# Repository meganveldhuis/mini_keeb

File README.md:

# Mini Keeb

## Hardware

### Components

- 16 Cherry MX Switches
- 2 rotary encoders
- 1 128x64 OLED (0.96")

### Schematic

### PCB

( slightly outdated screenshots )

## Software

coming soon

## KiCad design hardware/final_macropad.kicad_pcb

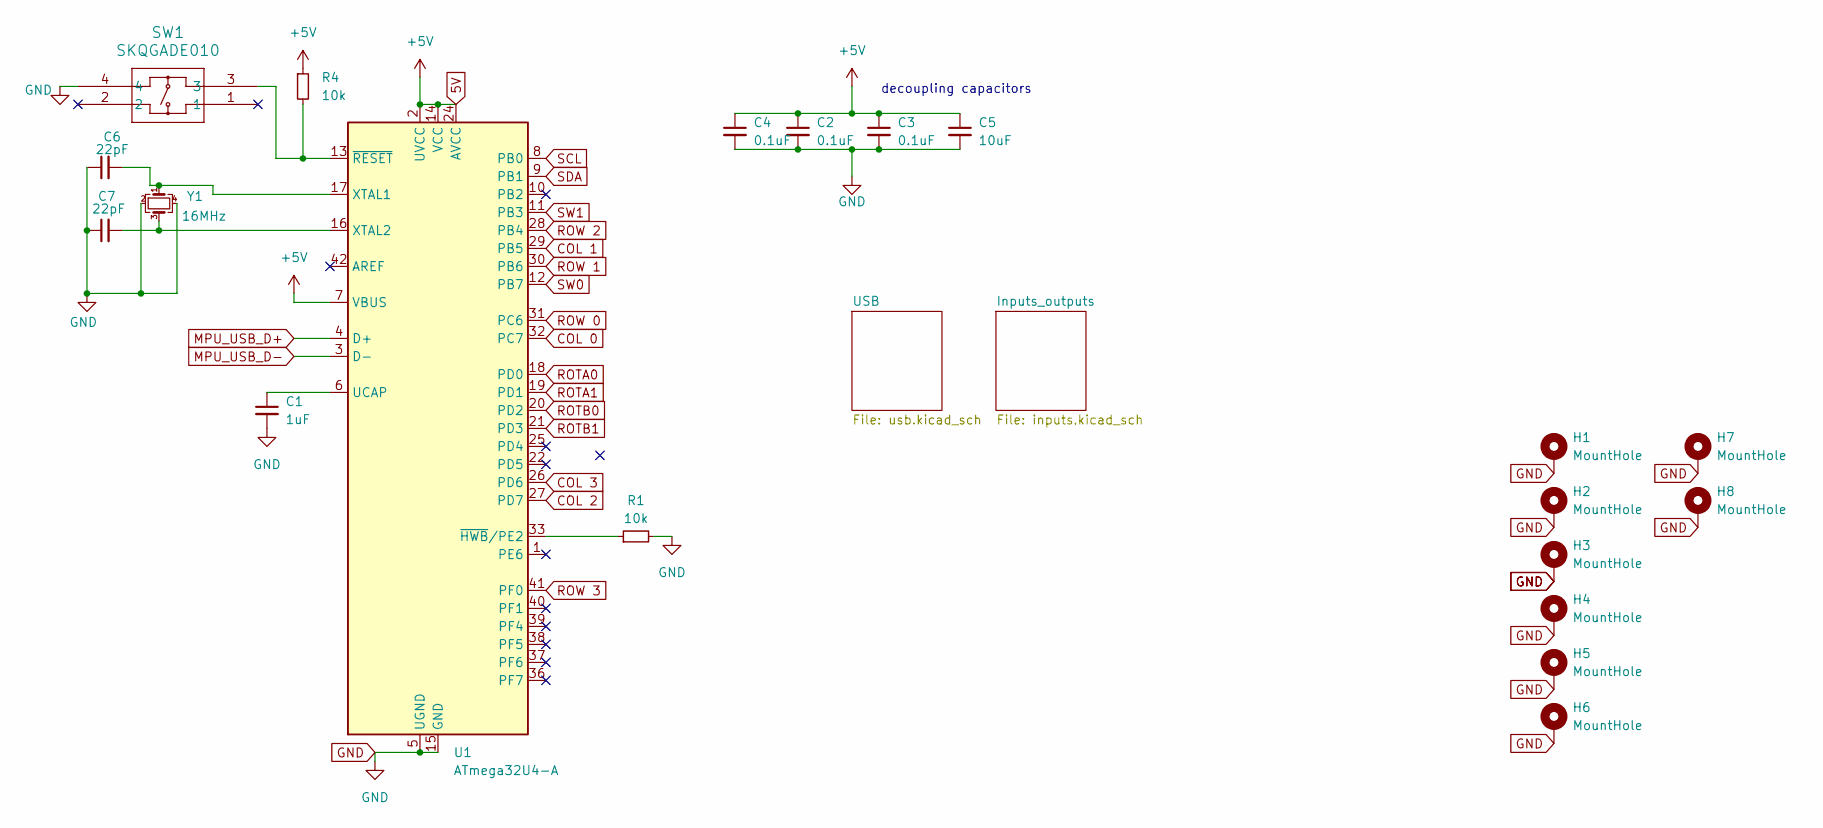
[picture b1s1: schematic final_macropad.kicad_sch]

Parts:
C1: 1uF; C_0402_1005Metric_Pad0.74x0.62mm_HandSolder
C2, C3, C4: 0.1uF; C_0402_1005Metric_Pad0.74x0.62mm_HandSolder
C5: 10uF; C_0603_1608Metric_Pad1.08x0.95mm_HandSolder
C6, C7: 22pF; C_0805_2012Metric
H1, H2, H3, H4: MountHole; MountingHole_3.2mm_M3_Pad_Via
H5, H6, H7, H8: MountHole; MountingHole_2.2mm_M2_Pad
R1, R4: 10k; R_0805_2012Metric
SW1: SKQGADE010; SKQGADE010_AAL
U1: ATmega32U4-A; TQFP-44_10x10mm_P0.8mm
Y1: 16MHz; Crystal_SMD_3225-4Pin_3.2x2.5mm

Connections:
5V: C2.1, C3.1, C4.1, C5.1, R4.1, U1.2 (UVCC), U1.7 (VBUS), U1.14 (VCC), U1.24 (AVCC), U1.34 (VCC), U1.44 (AVCC); also elsewhere on the board
COL 0: U1.32 (PC7); also elsewhere on the board
COL 1: U1.29 (PB5); also elsewhere on the board
COL 2: U1.27 (PD7); also elsewhere on the board
COL 3: U1.26 (PD6); also elsewhere on the board
GND: C1.2, C2.2, C3.2, C4.2, C5.2, C6.1, C7.1, H1.1, H2.1, H3.1, H4.1, H5.1, H6.1, H7.1, H8.1, R1.2, SW1.4, U1.5 (UGND), U1.15 (GND), U1.23 (GND), U1.35 (GND), U1.43 (GND), Y1.2, Y1.4; also elsewhere on the board
MPU_USB_D+: U1.4 (D+); also elsewhere on the board
MPU_USB_D-: U1.3 (D-); also elsewhere on the board
unnamed: C1.1, U1.6 (UCAP)
unnamed: C6.2, U1.17 (XTAL1), Y1.1
unnamed: C7.2, U1.16 (XTAL2), Y1.3
unnamed: R1.1, U1.33 (~HWB/PE2)
unnamed: R4.2, SW1.3, U1.13 (~RESET)
ROTA0: U1.18 (PD0); also elsewhere on the board
ROTA1: U1.19 (PD1); also elsewhere on the board
ROTB0: U1.20 (PD2); also elsewhere on the board
ROTB1: U1.21 (PD3); also elsewhere on the board
ROW 0: U1.31 (PC6); also elsewhere on the board
ROW 1: U1.30 (PB6); also elsewhere on the board
ROW 2: U1.28 (PB4); also elsewhere on the board
ROW 3: U1.41 (PF0); also elsewhere on the board
SCL: U1.8 (PB0); also elsewhere on the board
SDA: U1.9 (PB1); also elsewhere on the board
SW0: U1.12 (PB7); also elsewhere on the board
SW1: U1.11 (PB3); also elsewhere on the board

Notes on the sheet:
decoupling capacitors

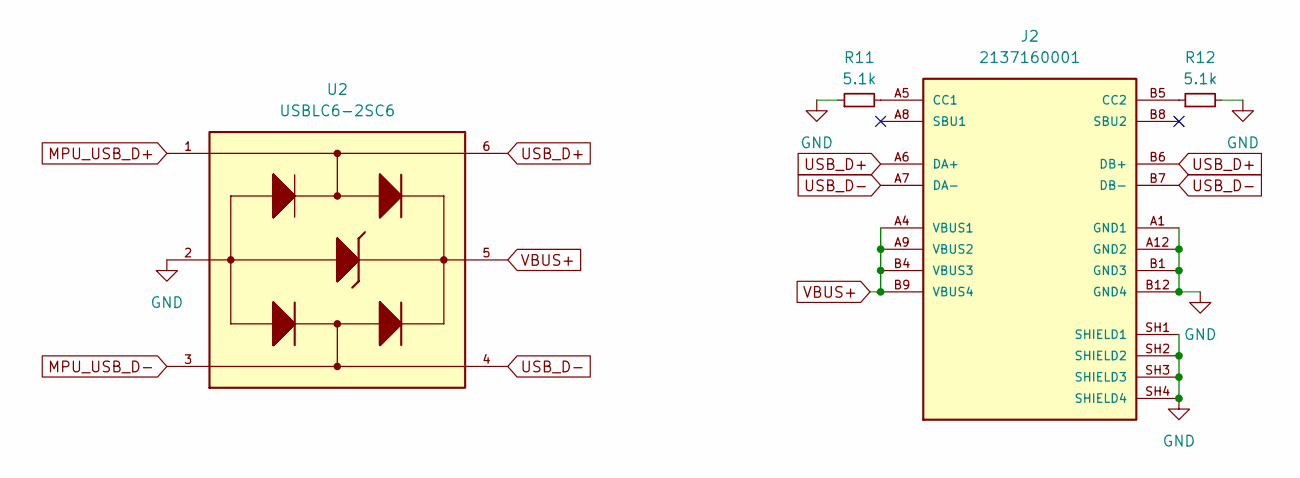
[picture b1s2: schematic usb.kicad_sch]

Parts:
J2: 2137160001; MOLEX_2137160001; PARTREV B
R11, R12: 5.1k; R_0805_2012Metric
U2: USBLC6-2SC6; SOT95P280X145-6N

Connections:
GND: J2.A1 (GND1), J2.A12 (GND2), J2.B1 (GND3), J2.B12 (GND4), J2.SH1 (SHIELD1), J2.SH2 (SHIELD2), J2.SH3 (SHIELD3), J2.SH4 (SHIELD4), R11.1, R12.2, U2.2; also elsewhere on the board
MPU_USB_D+: U2.1; also elsewhere on the board
MPU_USB_D-: U2.3; also elsewhere on the board
unnamed: J2.A5 (CC1), R11.2
unnamed: J2.B5 (CC2), R12.1
USB_D+: J2.A6 (DA+), J2.B6 (DB+), U2.6
USB_D-: J2.A7 (DA-), J2.B7 (DB-), U2.4
VBUS+: J2.A4 (VBUS1), J2.A9 (VBUS2), J2.B4 (VBUS3), J2.B9 (VBUS4), U2.5

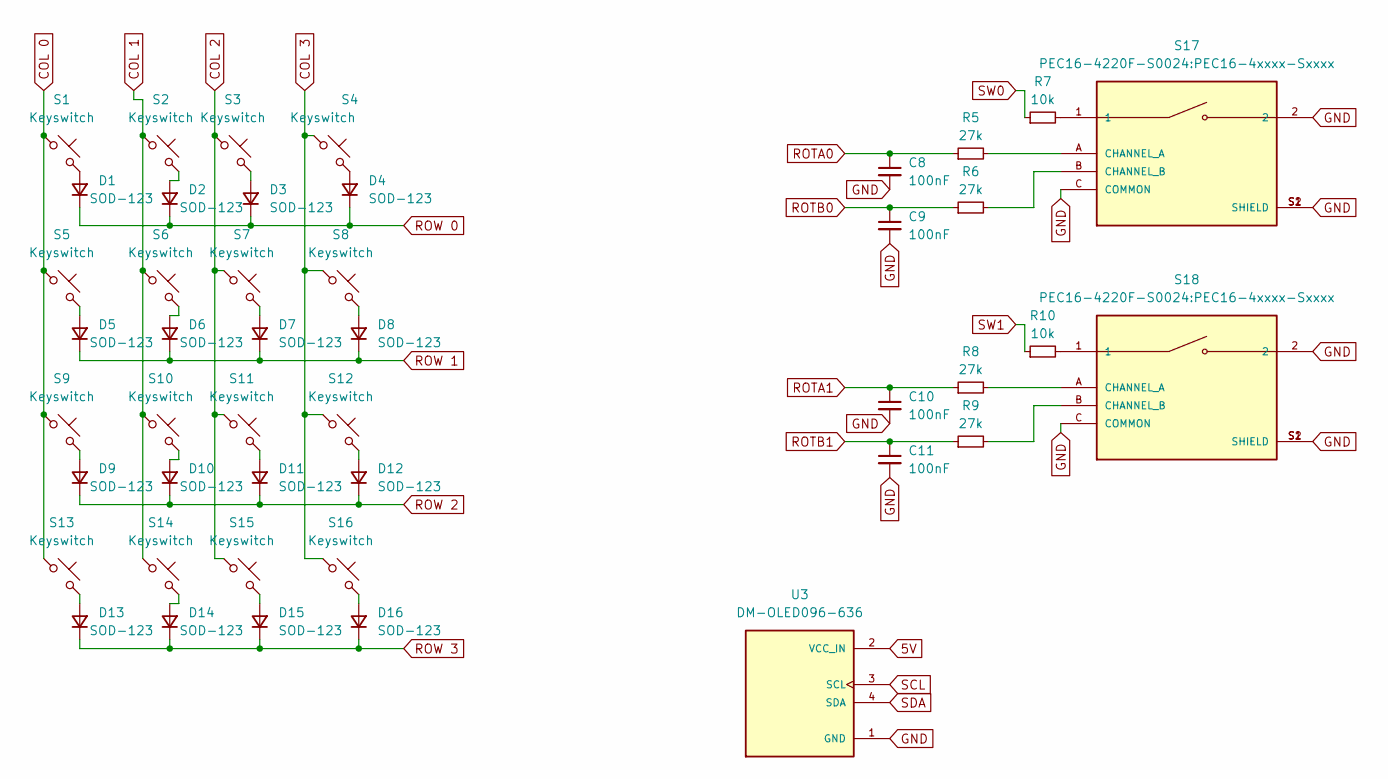
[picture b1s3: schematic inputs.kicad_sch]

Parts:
C8, C9, C10, C11: 100nF; C_0805_2012Metric
D1, D2, D3, D4, D5, D6, D7, D8, D9, D10, D11, D12, D13, D14, D15, D16: SOD-123; D_SOD-123
R5, R6, R8, R9: 27k; R_0805_2012Metric
R7, R10: 10k; R_0805_2012Metric
S1, S2, S3, S4, S5, S6, S7, S8, S9, S10, S11, S12, S13, S14, S15, S16: Keyswitch; SW_Cherry_MX_1.00u_PCB
S17, S18: PEC16-4220F-S0024:PEC16-4xxxx-Sxxxx; PEC16-4xxxx-Sxxxx; PARTREV 07/21
U3: DM-OLED096-636; MODULE_DM-OLED096-636; PARTREV 2018-09-10

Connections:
5V: U3.2 (VCC_IN); also elsewhere on the board
COL 0: S1.1, S5.1, S9.1, S13.1; also elsewhere on the board
COL 1: S2.1, S6.1, S10.1, S14.1; also elsewhere on the board
COL 2: S3.1, S7.1, S11.1, S15.1; also elsewhere on the board
COL 3: S4.1, S8.1, S12.1, S16.1; also elsewhere on the board
GND: C8.2, C9.2, C10.2, C11.2, S17.2, S17.C (COMMON), S17.S1 (SHIELD), S17.S2 (SHIELD), S18.2, S18.C (COMMON), S18.S1 (SHIELD), S18.S2 (SHIELD), U3.1 (GND), U3.S1, U3.S2, U3.S3, U3.S4; also elsewhere on the board
unnamed: D1.2 (A), S1.2
unnamed: D2.2 (A), S2.2
unnamed: D3.2 (A), S3.2
unnamed: D4.2 (A), S4.2
unnamed: D5.2 (A), S5.2
unnamed: D6.2 (A), S6.2
unnamed: D7.2 (A), S7.2
unnamed: D8.2 (A), S8.2
unnamed: D9.2 (A), S9.2
unnamed: D10.2 (A), S10.2
unnamed: D11.2 (A), S11.2
unnamed: D12.2 (A), S12.2
unnamed: D13.2 (A), S13.2
unnamed: D14.2 (A), S14.2
unnamed: D15.2 (A), S15.2
unnamed: D16.2 (A), S16.2
unnamed: R7.2, S17.1
unnamed: R10.2, S18.1
unnamed: R5.2, S17.A (CHANNEL_A)
unnamed: R6.2, S17.B (CHANNEL_B)
unnamed: R8.2, S18.A (CHANNEL_A)
unnamed: R9.2, S18.B (CHANNEL_B)
ROTA0: C8.1, R5.1; also elsewhere on the board
ROTA1: C10.1, R8.1; also elsewhere on the board
ROTB0: C9.1, R6.1; also elsewhere on the board
ROTB1: C11.1, R9.1; also elsewhere on the board
ROW 0: D1.1 (K), D2.1 (K), D3.1 (K), D4.1 (K); also elsewhere on the board
ROW 1: D5.1 (K), D6.1 (K), D7.1 (K), D8.1 (K); also elsewhere on the board
ROW 2: D9.1 (K), D10.1 (K), D11.1 (K), D12.1 (K); also elsewhere on the board
ROW 3: D13.1 (K), D14.1 (K), D15.1 (K), D16.1 (K); also elsewhere on the board
SCL: U3.3 (SCL); also elsewhere on the board
SDA: U3.4 (SDA); also elsewhere on the board
SW0: R7.1; also elsewhere on the board
SW1: R10.1; also elsewhere on the board

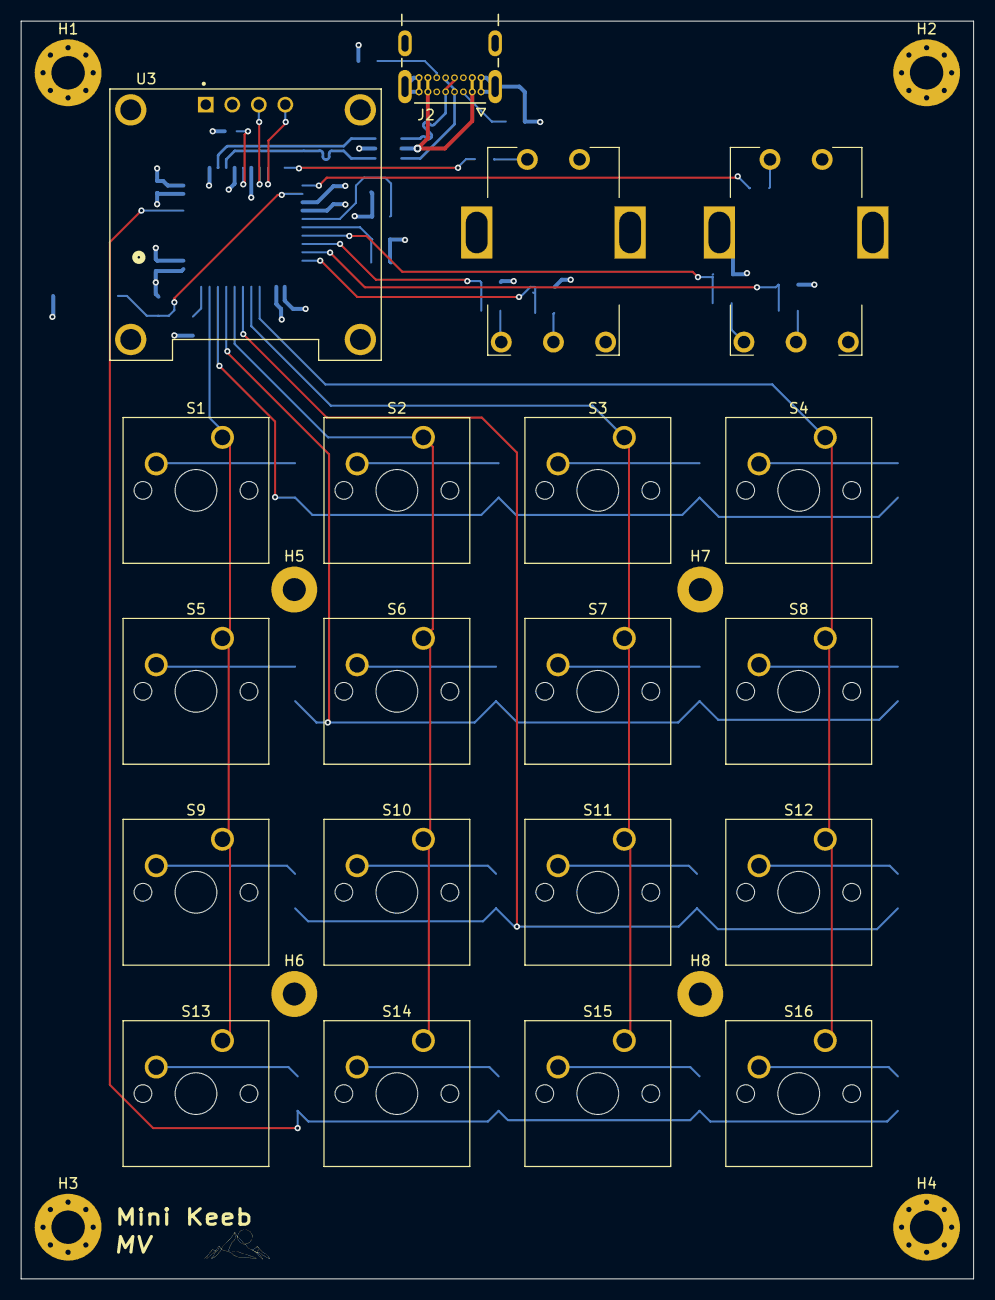
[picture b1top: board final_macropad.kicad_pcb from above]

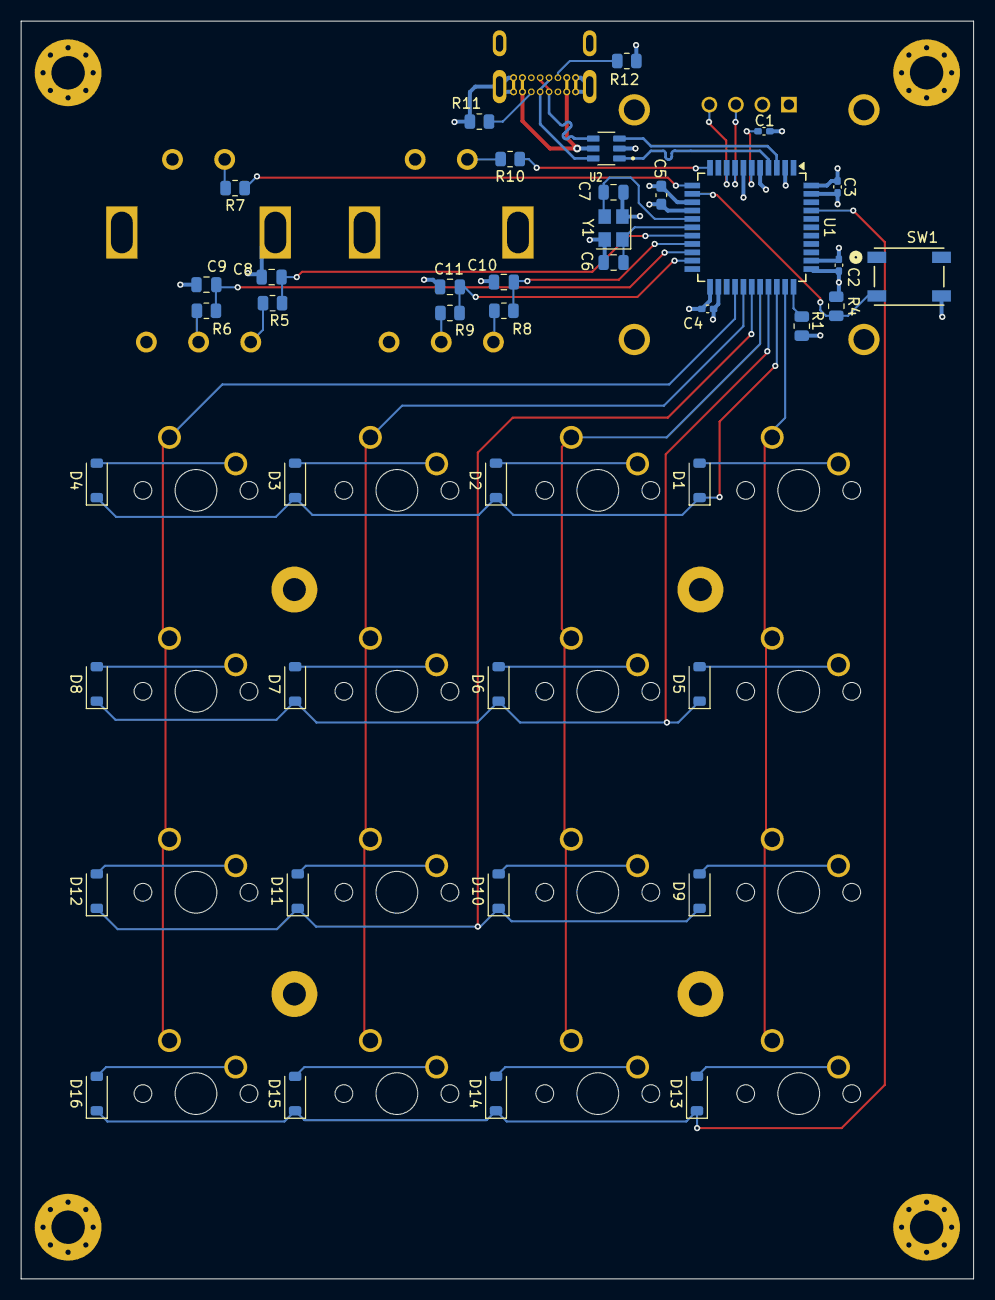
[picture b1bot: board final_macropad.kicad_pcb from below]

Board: 4 copper layers, 91.2 x 120.5 mm, 69 parts (41 on the bottom side), 52 nets.

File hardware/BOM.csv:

,,PART,AMT,,PRICE per unit,PART PRICE,LINK,
TRUE,"D1, D2, D3, D4, D5, D6, D7, D8, D9, D10,D11, D12, D13, D14, D15, D16",SOD123 Diode,16,160,$0.15,$2.40,https://www.digikey.ca/en/products/detail/diodes-incorporate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,
TRUE,"S17, S18",PEC16 rot encoder,2,20,$3.15,$6.30,https://www.digikey.ca/en/products/detail/bourns-inc/PEC16-4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,https://www.digikey.ca/en/products/detail/bourns-inc/PEC16-4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 
TRUE,S1-S16,MX Switches,16,160,,$0.00,,
TRUE,C1,1uF cap (0402),1,10,$0.12,$0.12,https://www.digikey.ca/en/products/detail/taiyo-yuden/JMK105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,
TRUE,"C2, C3, C4",0.1uF cap (0402),3,30,$0.12,$0.36,https://www.digikey.ca/en/products/detail/samsung-electro-me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,
TRUE,C5,10uF cap (0603),1,10,$0.21,$0.21,https://www.digikey.ca/en/products/detail/murata-electronics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,
TRUE,"C6, C7",22pF cap (0805),2,20,$0.15,$0.30,https://www.digikey.ca/en/products/detail/kemet/C0805C220J5G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,
TRUE,"C8, C9, C10, C11",100nF cap (0805),4,40,$0.47,$1.88,https://www.digikey.ca/en/products/detail/vishay-sprague/TMC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,
TRUE,U3,"OLED 128x64 (0.96"")",1,10,$12.00,$12.00,https://www.amazon.ca/128X64-Serial-Display-Module-White/dp/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,https://www.digikey.ca/en/products/detail/adafruit-industrie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
TRUE,"R1, R4, R7, R10",10k resistor (0805),4,40,$0.16,$0.64,https://www.digikey.ca/en/products/detail/susumu/RR1220P-103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,
TRUE,"R5, R6, R8, R9",27k resistor (0805),4,40,$0.16,$0.64,https://www.digikey.ca/en/products/detail/stackpole-electron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,
FALSE,SW1,low-profile switch,1,10,$0.31,$0.31,https://www.digikey.ca/en/products/detail/alps-alpine/SKQGAD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,
TRUE,U1,ATMega32U4-A,1,10,$8.30,$8.30,https://www.digikey.ca/en/products/detail/microchip-technolo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,
FALSE,J2,USB-C connector (Molex-2137160001),1,10,$2.12,$2.12,https://www.digikey.ca/en/products/detail/molex/2137160001/1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,
TRUE,Y1,16MHz crystal (SMD 3225-4pin),1,10,$0.61,$0.61,https://www.digikey.ca/en/products/detail/epson/TSX-3225-16-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,
FALSE,U2,USBLC6-2SC6,1,10,$0.36,$0.36,https://www.digikey.ca/en/products/detail/stmicroelectronics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,
,,,,,,,,
,,,,,TOTAL,34.46,,

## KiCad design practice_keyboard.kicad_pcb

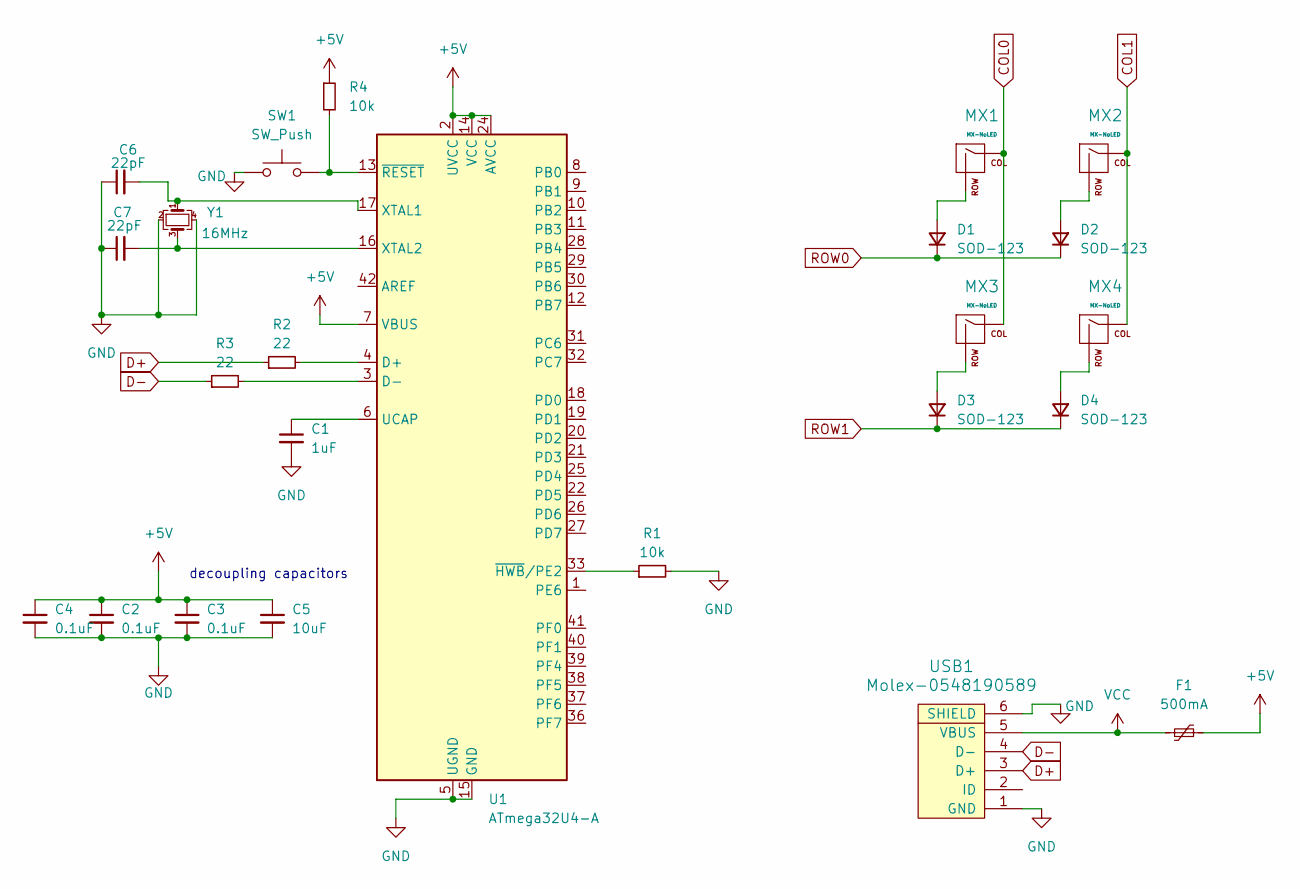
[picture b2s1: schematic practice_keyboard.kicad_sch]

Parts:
C1: 1uF; C_0805_2012Metric
C2, C3, C4: 0.1uF; C_0805_2012Metric
C5: 10uF; C_0805_2012Metric
C6, C7: 22pF; C_0805_2012Metric
D1, D2, D3, D4: SOD-123; D_SOD-123
F1: 500mA; Fuse_1206_3216Metric
MX1, MX2, MX3, MX4: MX-NoLED; MX-1U
R1, R4: 10k; R_0805_2012Metric
R2, R3: 22; R_0805_2012Metric
SW1: SW_Push; SKQG-1155865
U1: ATmega32U4-A; TQFP-44_10x10mm_P0.8mm
USB1: Molex-0548190589
Y1: 16MHz; Crystal_SMD_3225-4Pin_3.2x2.5mm

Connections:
+5V: C2.1, C3.1, C4.1, C5.1, F1.2, R4.1, U1.2 (UVCC), U1.7 (VBUS), U1.14 (VCC), U1.24 (AVCC), U1.34 (VCC), U1.44 (AVCC)
COL0: MX1.1 (COL), MX3.1 (COL)
COL1: MX2.1 (COL), MX4.1 (COL)
D+: R2.1, USB1.3 (D+)
D-: R3.1, USB1.4 (D-)
GND: C1.2, C2.2, C3.2, C4.2, C5.2, C6.1, C7.1, R1.2, SW1.1, U1.5 (UGND), U1.15 (GND), U1.23 (GND), U1.35 (GND), U1.43 (GND), USB1.1 (GND), USB1.6 (SHIELD), Y1.2, Y1.4
unnamed: D1.2 (A), MX1.2 (ROW)
unnamed: D2.2 (A), MX2.2 (ROW)
unnamed: D3.2 (A), MX3.2 (ROW)
unnamed: D4.2 (A), MX4.2 (ROW)
unnamed: R2.2, U1.4 (D+)
unnamed: R3.2, U1.3 (D-)
unnamed: C1.1, U1.6 (UCAP)
unnamed: C6.2, U1.17 (XTAL1), Y1.1
unnamed: C7.2, U1.16 (XTAL2), Y1.3
unnamed: R1.1, U1.33 (~HWB/PE2)
unnamed: R4.2, SW1.2, U1.13 (~RESET)
ROW0: D1.1 (K), D2.1 (K)
ROW1: D3.1 (K), D4.1 (K)
VCC: F1.1, USB1.5 (VBUS)

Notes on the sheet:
decoupling capacitors

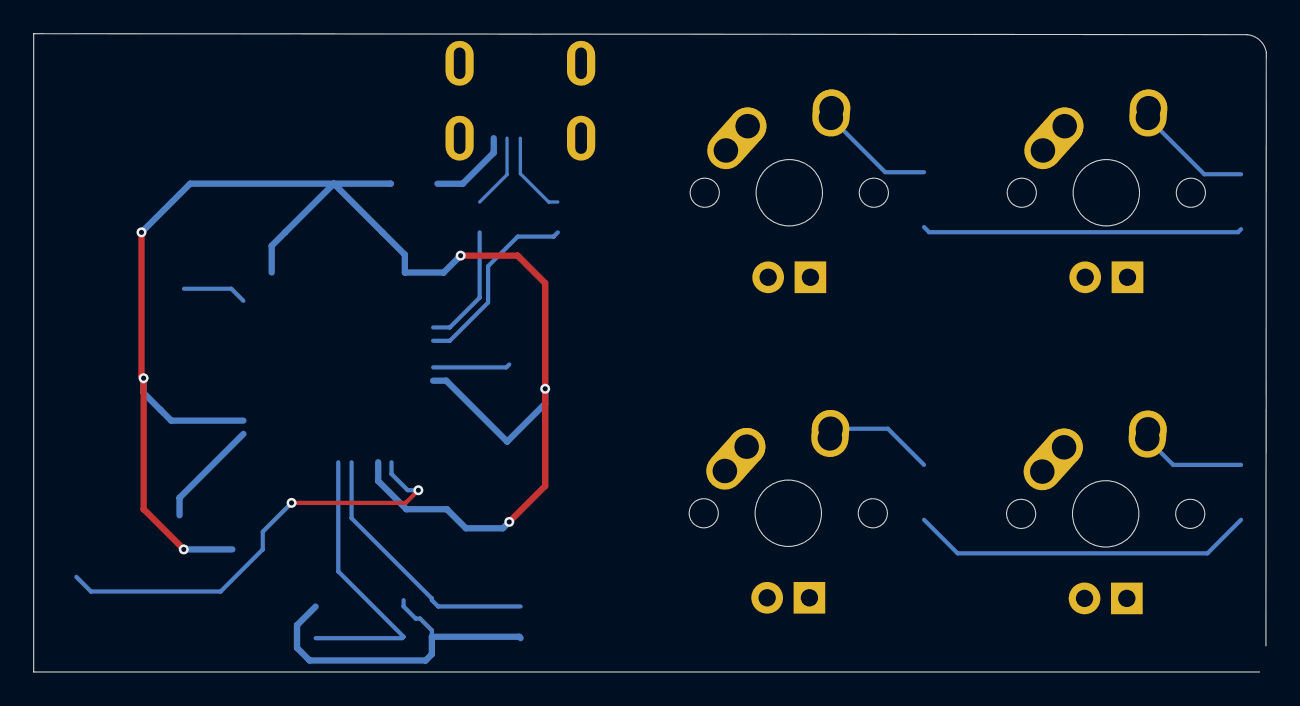
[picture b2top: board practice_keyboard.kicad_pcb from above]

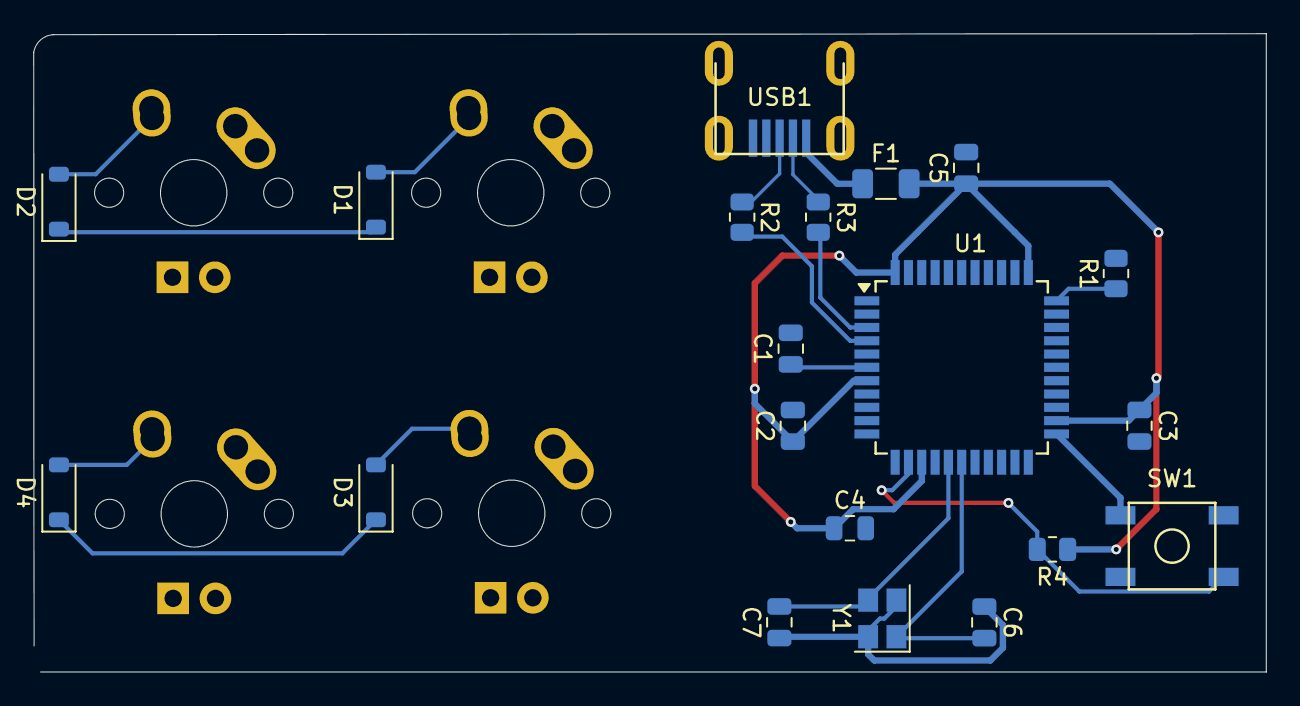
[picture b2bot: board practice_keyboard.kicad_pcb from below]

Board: 2 copper layers, 74.1 x 38.4 mm, 24 parts (20 on the bottom side), 20 nets.

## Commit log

2025-03-04 add schematic and unrouted pcb
2025-05-20 updated PCB to be most recent edition
2025-05-24 organize schematic and add USB-C and surge protector
2025-05-25 remove old diodes
2025-05-26 fix switches to be correct order and move diodes
2025-05-26 route USBC connector
2025-05-28 route USB and rotary encoder
2025-05-28 update PCB routing
2025-05-29 route all switches
2025-05-29 check DRC
2025-05-31 update BOM
2025-05-31 update BOM and reset button footprint
2025-05-31 update BOM and add to silkscreen
2025-06-08 rotate MCU, route reset button, crystal, and OLED
2025-06-08 reroute decoupling capacitors
2025-06-10 Finish rerouting
2025-06-10 increase trace width from USBC connector
2025-06-10 move trace away from through-hole
2025-06-13 build gerber files
2025-06-27 update pcb schematic
2025-07-02 Add README and update hardware in doc
